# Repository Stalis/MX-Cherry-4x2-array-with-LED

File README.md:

# MX Cherry 4x2

## PCB Renders

Compact 8-key Cherry MX keyboard module: 4 columns x 2 rows. It has no onboard microcontroller and is intended for connection to an external controller or breadboard.

## Features

- 8 Cherry MX 1U, PCB-mount switch footprints on a 19.05 mm pitch.
- 4x2 switch matrix with one diode per key.
- Independent 4x2 LED matrix with one LED per key.
- Two parallel SMD socket connectors, `J1` and `J2`: 2x10, 2.54 mm pitch, on the bottom side of the board.
- Two-layer, 1.6 mm thick PCB measuring 78.74 x 38.10 mm.

## Matrices

Key layout:

|       | `COL_0` | `COL_1` | `COL_2` | `COL_3` |
| --- | --- | --- | --- | --- |
| `ROW_0` | SW1 / D1 / RLED1 | SW2 / D2 / RLED2 | SW3 / D3 / RLED3 | SW4 / D4 / RLED4 |
| `ROW_1` | SW5 / D5 / RLED5 | SW6 / D6 / RLED6 | SW7 / D7 / RLED7 | SW8 / D8 / RLED8 |

Each key has a series diode, `D1` through `D8`, to prevent ghosting during matrix scanning. LEDs `RLED1` through `RLED8` form an independent matrix with the same four columns and two rows.

## Connections

`J1` and `J2` are electrically identical: use either connector, or both to mount the module. Pin numbering follows the standard 2x10 connector convention: odd pins are on one row and even pins on the other.

| Pin | Signal | Function |
| --- | --- | --- |
| 1 | `SW_0_ROW_0` | switch-matrix row 0 |
| 2 | `LED_0_ROW_0` | LED-matrix row 0 |
| 3 | `SW_0_ROW_1` | switch-matrix row 1 |
| 4 | `LED_0_ROW_1` | LED-matrix row 1 |
| 5-12 | NC | not connected |
| 13 | `SW_0_COL_0` | switch-matrix column 0 |
| 14 | `LED_0_COL_0` | LED-matrix column 0 |
| 15 | `SW_0_COL_1` | switch-matrix column 1 |
| 16 | `LED_0_COL_1` | LED-matrix column 1 |
| 17 | `SW_0_COL_2` | switch-matrix column 2 |
| 18 | `LED_0_COL_2` | LED-matrix column 2 |
| 19 | `SW_0_COL_3` | switch-matrix column 3 |
| 20 | `LED_0_COL_3` | LED-matrix column 3 |

The controller must scan both matrices externally. The PCB has no LED current-limiting resistors; use an external current-limiting circuit or LED driver.

## Components

| Quantity | References | Footprint |
| --- | --- | --- |
| 8 | `SW1-SW8` | Cherry MX 1U, PCB mount |
| 8 | `D1-D8` | SOD-323F |
| 8 | `RLED1-RLED8` | LED 1206, 3216 Metric |
| 2 | `J1`, `J2` | SMD socket 2x10, 2.54 mm |

The schematic does not specify diode ratings or LED color and electrical parameters. Select them for the voltage and current of the external driver.

## DRC Notes

The following DRC findings are expected for this layout and should be excluded individually with a comment in KiCad after mechanical clearance is confirmed. Do not disable these checks globally.

| DRC check | Count | Rationale |
| --- | --- | --- |
| `npth_inside_courtyard` | 8 | The Cherry MX locating holes are through-holes, while `J1` and `J2` are bottom-side SMD connectors. The overlaps are courtyard-only; verify the connector body and pads clear the switch locating pins. |
| `courtyards_overlap` | 8 | Each top-side LED is intentionally placed at its associated switch for backlighting. |
| `footprint_symbol_field_mismatch` | 8 warnings | Diodes `D1-D8` have a schematic-only `Sim.Device` field that is absent from their footprints. This does not affect fabrication or electrical connectivity. |

## Repository Files

- `MX Cherry 4x2.kicad_pro` - KiCad project.
- `MX Cherry 4x2.kicad_sch` - main schematic.
- `MX Cherry 4x2.kicad_pcb` - PCB layout.
- `switch_module.kicad_sch` and `led_module.kicad_sch` - reusable sheets for one switch with a diode and one LED.
- `jlcpcb/` and `production/` - previously exported manufacturing files.

> The BOM and CPL files in `jlcpcb/` and `production/` are outdated relative to the current schematic and PCB. They omit `RLED1` through `RLED8` and describe the connectors as 1x10. Re-export Gerbers, BOM, and CPL from the current project before ordering.

## Opening and Checking

The project was created with KiCad 10. Open `MX Cherry 4x2.kicad_pro` in KiCad, or check it from the command line:

```sh
/Applications/KiCad/KiCad.app/Contents/MacOS/kicad-cli sch erc "MX Cherry 4x2.kicad_sch"
/Applications/KiCad/KiCad.app/Contents/MacOS/kicad-cli pcb drc --schematic-parity "MX Cherry 4x2.kicad_pcb"
```

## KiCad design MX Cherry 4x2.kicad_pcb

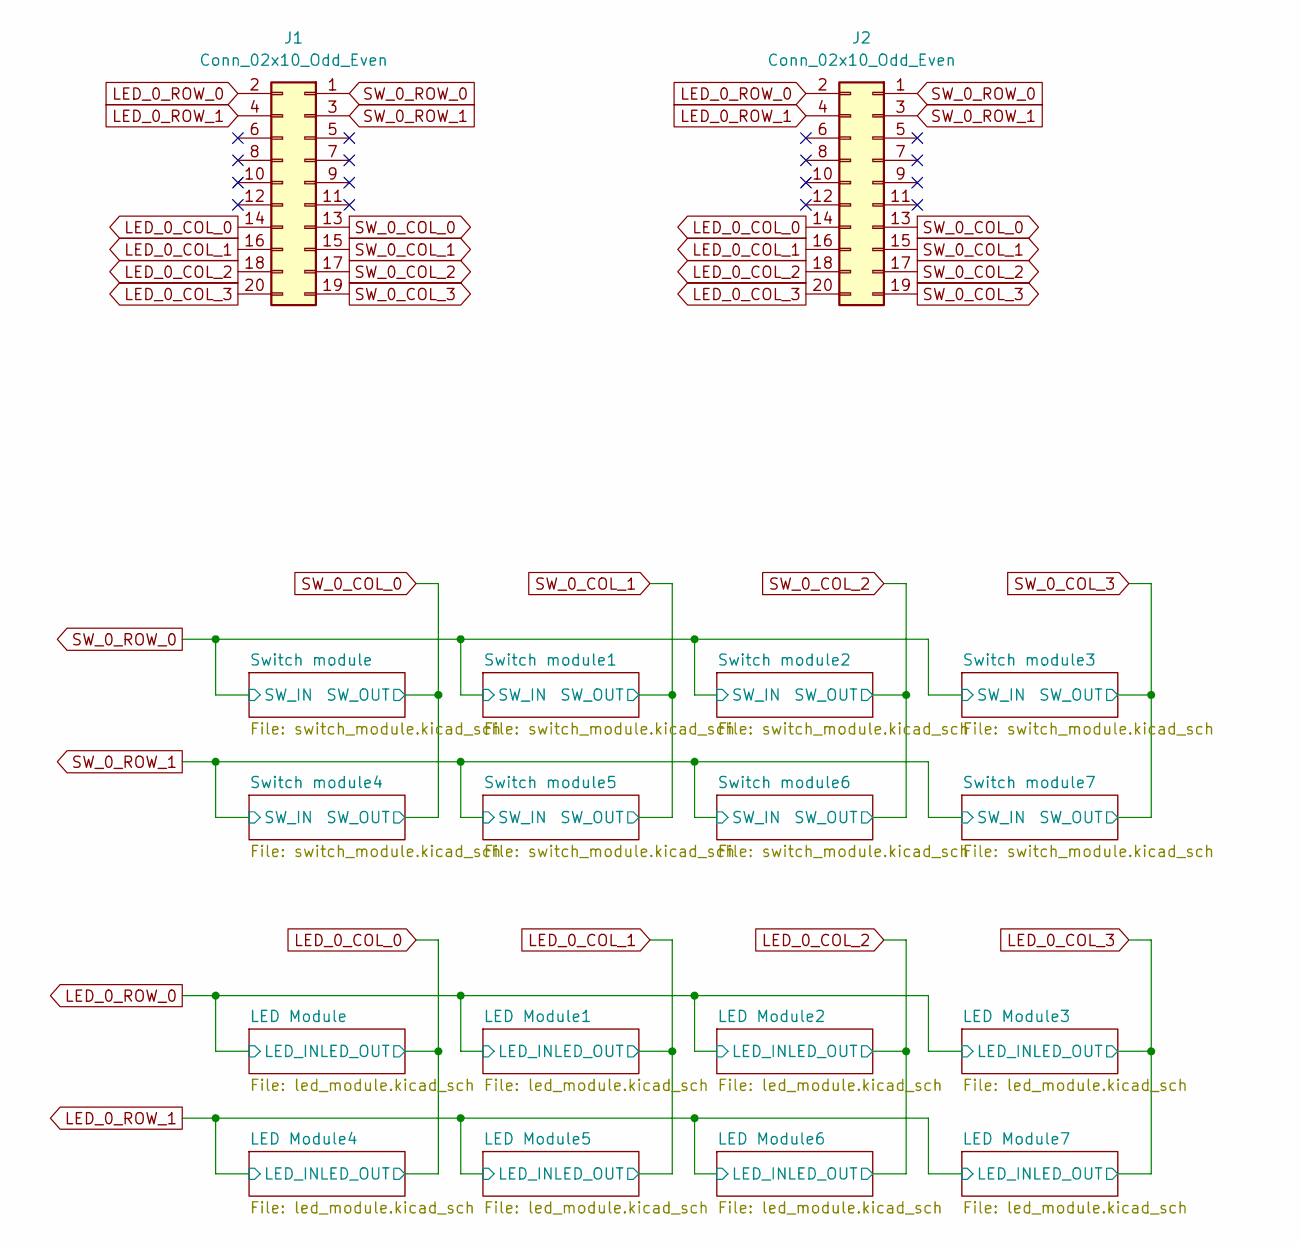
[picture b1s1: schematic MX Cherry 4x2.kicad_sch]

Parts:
J1, J2: Conn_02x10_Odd_Even; PinSocket_2x10_P2.54mm_Vertical_SMD

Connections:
LED_0_COL_0: J1.14, J2.14; also elsewhere on the board
LED_0_COL_1: J1.16, J2.16; also elsewhere on the board
LED_0_COL_2: J1.18, J2.18; also elsewhere on the board
LED_0_COL_3: J1.20, J2.20; also elsewhere on the board
LED_0_ROW_0: J1.2, J2.2; also elsewhere on the board
LED_0_ROW_1: J1.4, J2.4; also elsewhere on the board
SW_0_COL_0: J1.13, J2.13; also elsewhere on the board
SW_0_COL_1: J1.15, J2.15; also elsewhere on the board
SW_0_COL_2: J1.17, J2.17; also elsewhere on the board
SW_0_COL_3: J1.19, J2.19; also elsewhere on the board
SW_0_ROW_0: J1.1, J2.1; also elsewhere on the board
SW_0_ROW_1: J1.3, J2.3; also elsewhere on the board

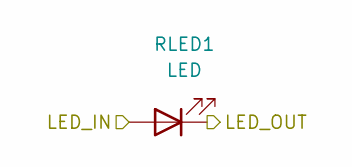
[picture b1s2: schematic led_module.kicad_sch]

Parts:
RLED1: LED; LED_1206_3216Metric_Pad1.42x1.75mm_HandSolder

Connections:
LED_0_COL_0: RLED1.1 (K); also elsewhere on the board
LED_0_ROW_0: RLED1.2 (A); also elsewhere on the board

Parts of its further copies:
RLED2, RLED3, RLED4, RLED5, RLED6, RLED7, RLED8: LED; LED_1206_3216Metric_Pad1.42x1.75mm_HandSolder

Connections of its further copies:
LED_0_COL_0: RLED5.1 (K); also elsewhere on the board
LED_0_COL_1: RLED2.1 (K), RLED6.1 (K); also elsewhere on the board
LED_0_COL_2: RLED3.1 (K), RLED7.1 (K); also elsewhere on the board
LED_0_COL_3: RLED4.1 (K), RLED8.1 (K); also elsewhere on the board
LED_0_ROW_0: RLED2.2 (A), RLED3.2 (A), RLED4.2 (A); also elsewhere on the board
LED_0_ROW_1: RLED5.2 (A), RLED6.2 (A), RLED7.2 (A), RLED8.2 (A); also elsewhere on the board

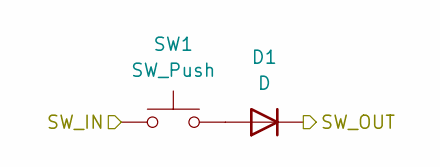
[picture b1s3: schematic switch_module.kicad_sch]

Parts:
D1: D; D_SOD-323F
SW1: SW_Push; SW_Cherry_MX_1.00u_PCB

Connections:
unnamed: D1.2 (A), SW1.2
SW_0_COL_0: D1.1 (K); also elsewhere on the board
SW_0_ROW_0: SW1.1; also elsewhere on the board

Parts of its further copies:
D2, D3, D4, D5, D6, D7, D8: D; D_SOD-323F
SW2, SW3, SW4, SW5, SW6, SW7, SW8: SW_Push; SW_Cherry_MX_1.00u_PCB

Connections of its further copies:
unnamed: D2.2 (A), SW2.2
unnamed: D3.2 (A), SW3.2
unnamed: D4.2 (A), SW4.2
unnamed: D5.2 (A), SW5.2
unnamed: D6.2 (A), SW6.2
unnamed: D7.2 (A), SW7.2
unnamed: D8.2 (A), SW8.2
SW_0_COL_0: D5.1 (K); also elsewhere on the board
SW_0_COL_1: D2.1 (K), D6.1 (K); also elsewhere on the board
SW_0_COL_2: D3.1 (K), D7.1 (K); also elsewhere on the board
SW_0_COL_3: D4.1 (K), D8.1 (K); also elsewhere on the board
SW_0_ROW_0: SW2.1, SW3.1, SW4.1; also elsewhere on the board
SW_0_ROW_1: SW5.1, SW6.1, SW7.1, SW8.1; also elsewhere on the board

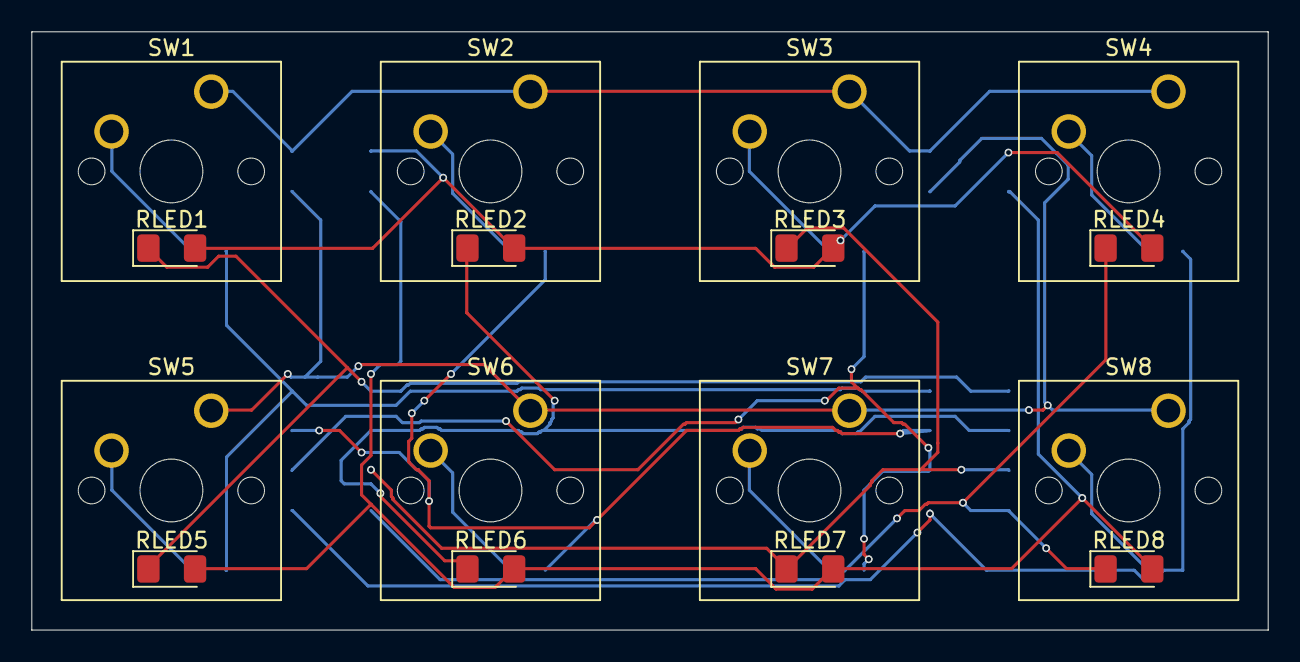
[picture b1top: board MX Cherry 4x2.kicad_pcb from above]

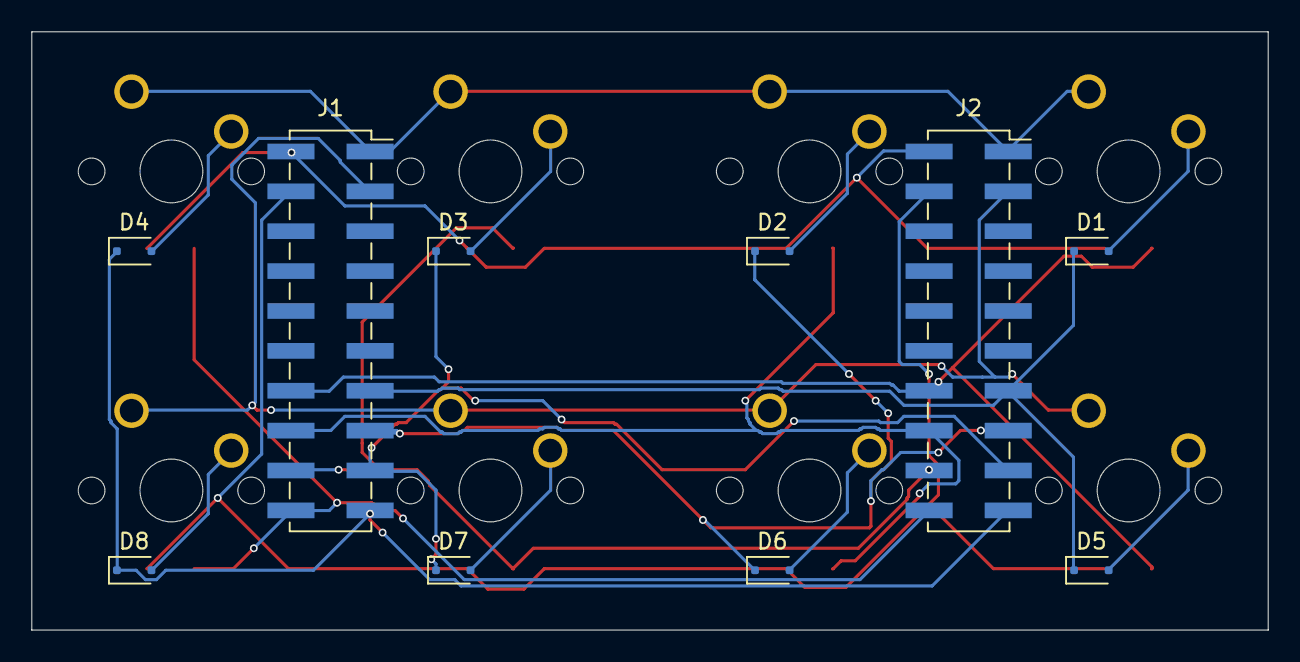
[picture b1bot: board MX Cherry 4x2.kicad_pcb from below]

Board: 2 copper layers, 78.7 x 38.1 mm, 26 parts (10 on the bottom side), 20 nets.
